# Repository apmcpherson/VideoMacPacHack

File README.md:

# VideoMacPacHack

The VideoMacPacHack is a clone of the Video Mac Pac, a PDS video card for the Macintosh Portable designed in 1991 by Computer Care Inc. The Video Mac Pac provides monochrome (1-bit) video on an external display, with several resolutions selectable by a control panel.

The VideoMacPacHack aims to replicate the Video Mac Pac using original parts where possible, with modern substitutions in  cases where original parts are hard to source (e.g. GAL, miniature relay), or where the original design was unknown (the video adapter board).

## Contents

* `hardware/VideoMacPac`: PCB design for the VideoMacPacHack, 4 layers, made in Kicad
* `hardware/VGA_adapter`: PCB design for the VGA breakout board, 2 layers, made in EAGLE
* `software`: Video Mac Pac Control Panel, needed to load the card firmware and select resolution
* `photos`: Photos of the original and clone card
* `documentation`: Technical information on the hardware and software

## System Requirements and Operation

The VideoMacPacHack fits the PDS slot of the Macintosh Portable. It has been successfully tested in both M5120 (non-backlit) and M5126 (backlit) Portables. Based on the address space used by the card, it will probably only work on Portables with less than 8MB of RAM installed.

The VideoMacPacHack (like the original Video Mac Pac) requires its associated control panel to run (see `software`). The external screen will become active when the control panel loads, provided the external video adapter is attached at boot. If the Portable is put to sleep, the external display will not work until reboot.

## Acknowledgments

The Video Mac Pac was created by Computer Care Inc. in 1991, apparently based on the Lapis DisplayServer.

The VideoMacPacHack was designed by [Andrew McPherson](https://github.com/apmcpherson) with encouragement from [Tom Stepleton](https://github.com/stepleton) based on hardware in his collection. In the interest of historical preservation it is released into the public domain, with no warranty of any sort.

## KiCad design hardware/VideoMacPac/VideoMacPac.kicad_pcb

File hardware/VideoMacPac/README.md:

# VideoMacPacHack

These design materials are in the public domain, with no warranty whatsoever. See `documentation` on this repository for further design notes.

## Kicad files

* `VideoMacPac.pro`: Kicad project
* `VideoMacPac.sch`: Kicad schematic
* `VideoMacPac.kicad_pcb`: Kicad PCB design
* `VideoMacPac_schematic.pdf`: Schematic in PDF format

## Gerbers

This a 4-layer PCB which can be fabricated from the files in the `gerbers` directory.

* `VideoMacPac-F.Cu.gbr`: top copper
* `VideoMacPac-In1.Cu.gbr`: inner layer 1 copper
* `VideoMacPac-In2.Cu.gbr`: inner layer 2 copper
* `VideoMacPac-B.Cu.gbr`: bottom copper
* `VideoMacPac-F.SilkS.gbr`: top silkscreen
* `VideoMacPac-F.Mask.gbr`: top soldermask
* `VideoMacPac-B.Mask.gbr`: bottom soldermask
* `VideoMacPac-Edge.Cuts.gbr`: board outline
* `VideoMacPac.drl`: Excellon drill file

## Bill of Materials

| Name    | Value                                |
| ------- | ------------------------------------ |
| C1-C8   | 0.1uF axial capacitors               |
| J1      | 20-pin IDC header                    |
| J2      | 96-pin right-angle EuroDIN           |
| R1-R4   | 4.7k resistors                       |
| RN1-RN2 | 3x47 ohm SIP resistor networks       |
| RN3-RN4 | 4x47 ohm SIP resistor networks       |
| U1      | XC2018-100-PC84 (faster can be used) |
| U2      | 74F521 (DIP)                         |
| U3      | 74AHCT1G00 (SOT23)                   |
| U4      | 74F244 (DIP) -- do not substitute    |
| U5-U8   | MT42C4064Z-12 (faster can be used)   |
| U9      | TPS2030 (DIP)                        |
| X1      | 36MHz 4-pin oscillator               |
| X2      | 50.35MHz 4-pin oscillator            |
| X3      | 57.2832MHz 4-pin oscillator          |

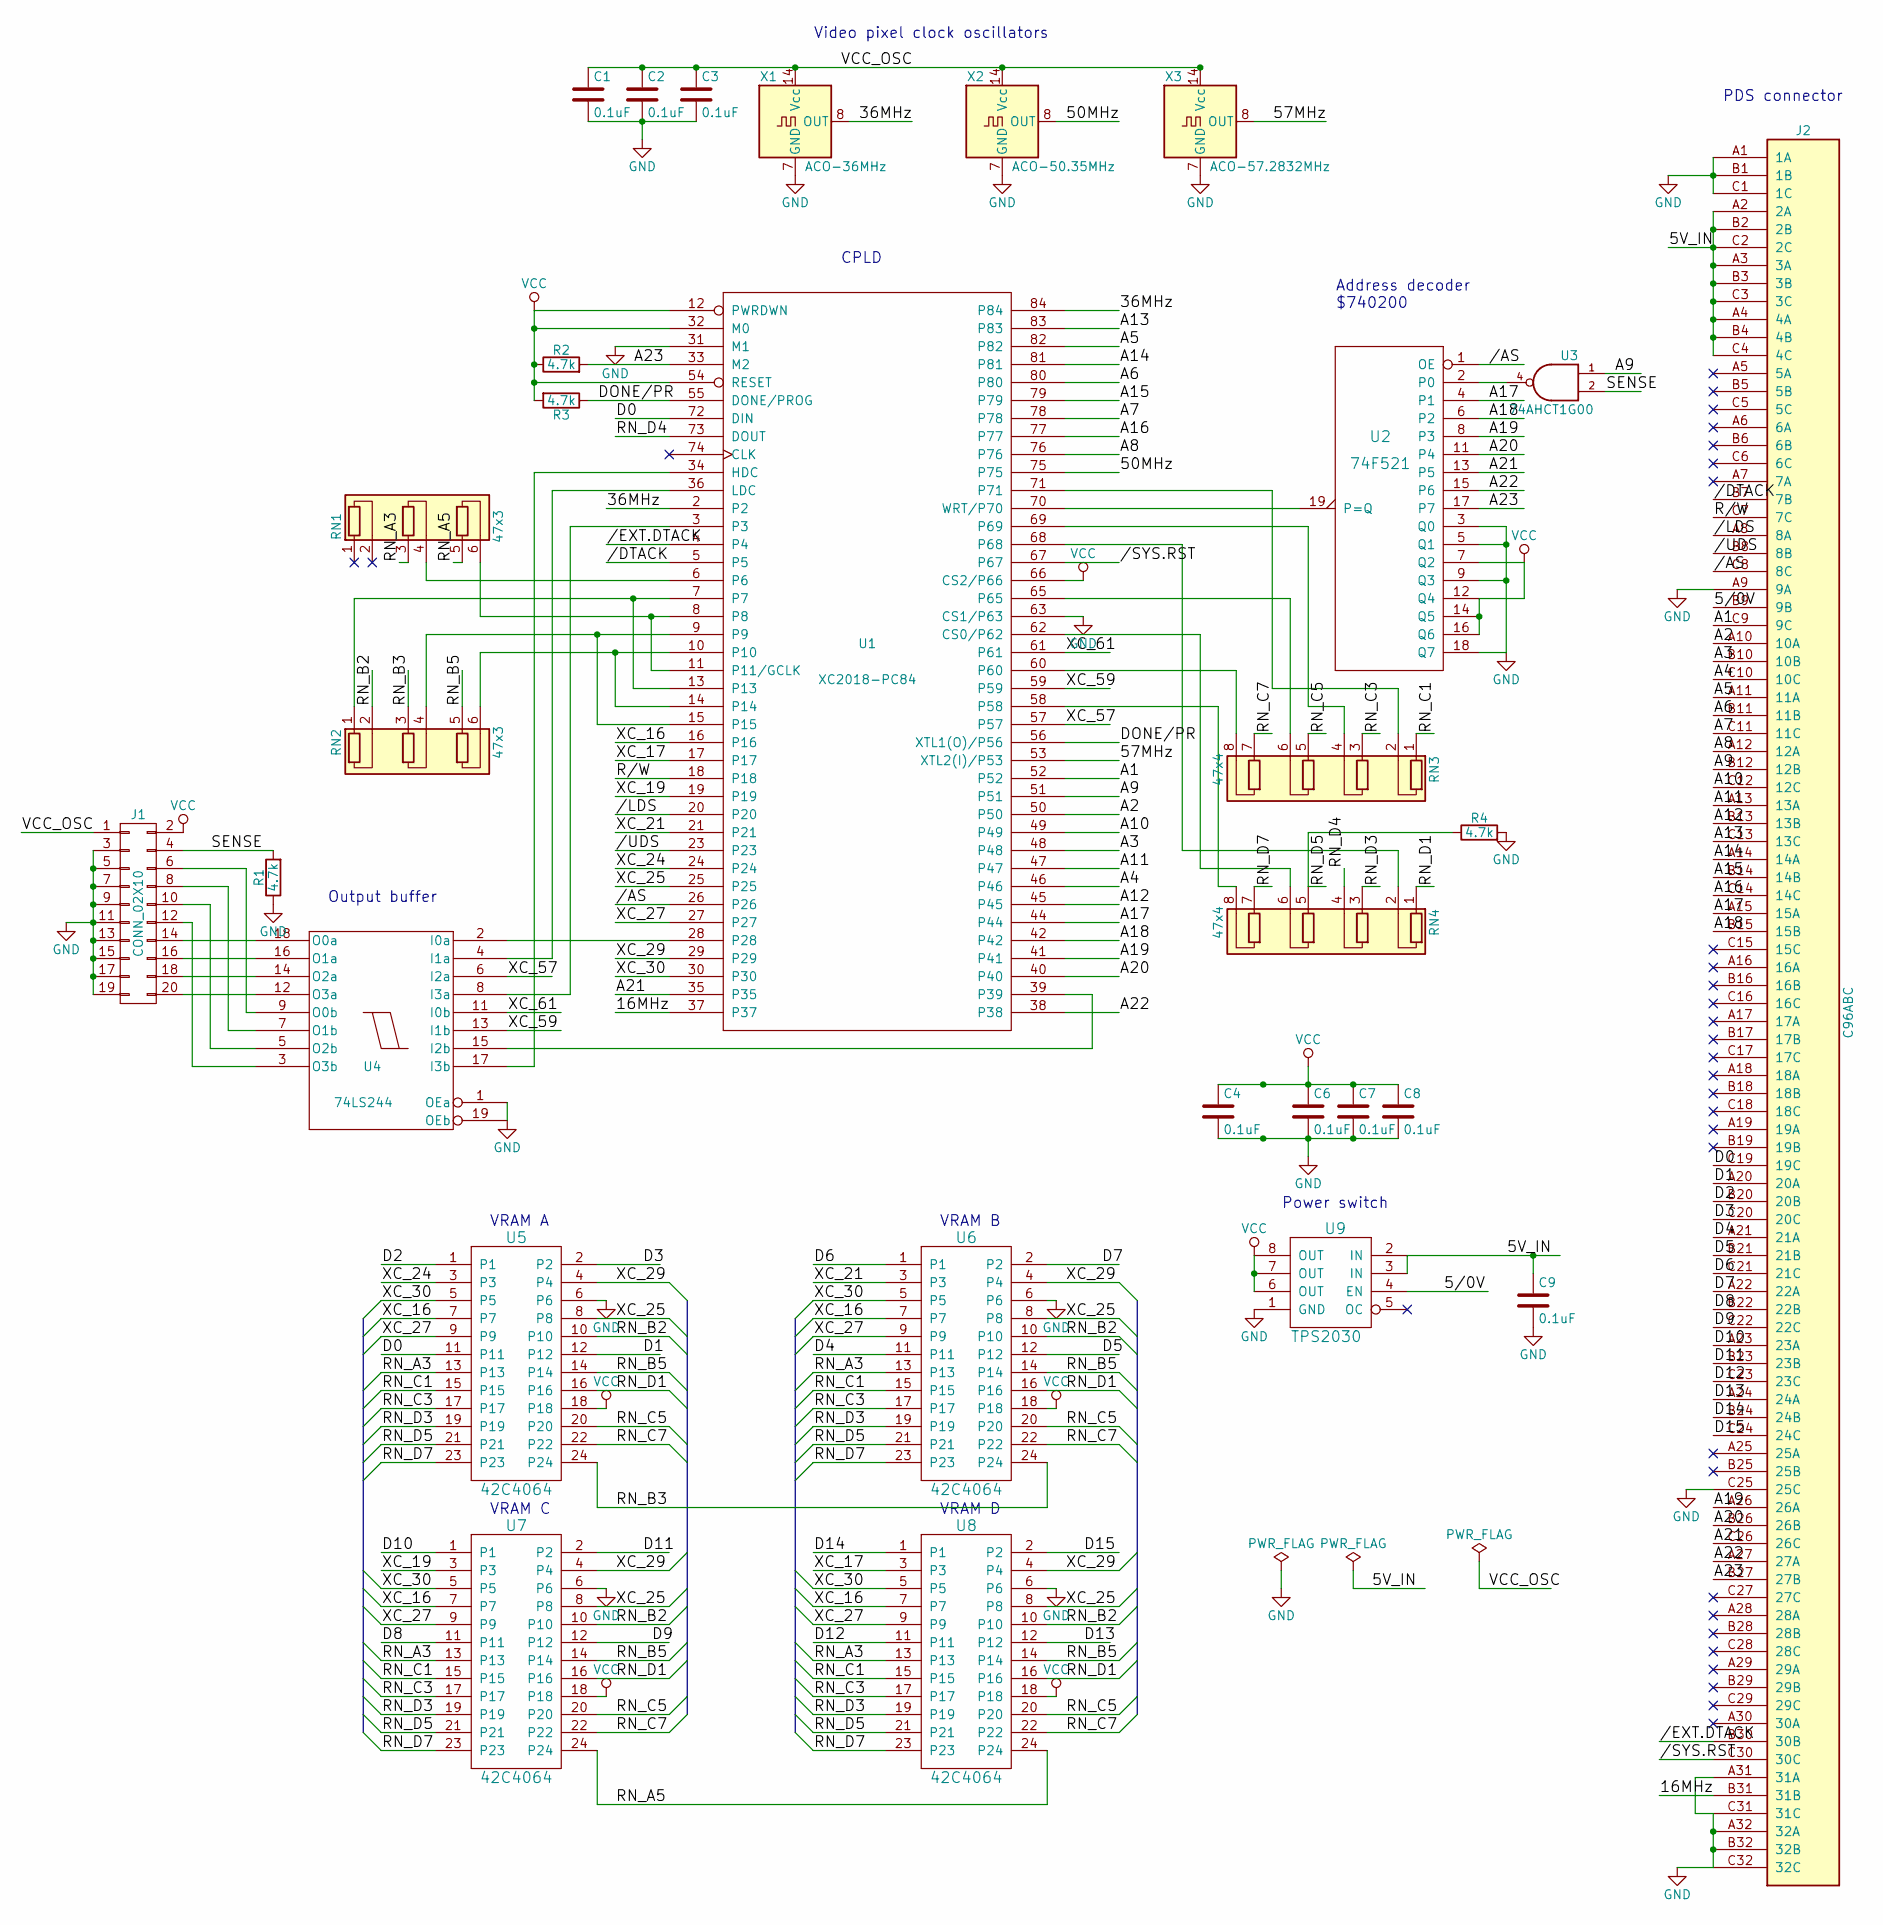
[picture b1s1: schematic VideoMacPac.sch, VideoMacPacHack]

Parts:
C1, C2, C3, C4, C6, C7, C8, C9: 0.1uF; C_Axial_L5.1mm_D3.1mm_P7.50mm_Horizontal
J1: CONN_02X10; IDC_Header_Straight_20pins
J2: C96ABC; C96ABCMD
R1, R2, R3, R4: 4.7k; R_Axial_DIN0207_L6.3mm_D2.5mm_P10.16mm_Horizontal
RN1, RN2: 47x3; R_Array_SIP6
RN3, RN4: 47x4; R_Array_SIP8
U1: XC2018-PC84; PLCC84
U2: 74F521; DIP-20_W7.62mm
U3: 74AHCT1G00; SOT-23-5
U4: 74LS244; DIP-20_W7.62mm
U5, U6, U7, U8: 42C4064; SIP24
U9: TPS2030; DIP-8_W7.62mm
X1: ACO-36MHz; Oscillator_DIP-14
X2: ACO-50.35MHz; Oscillator_DIP-14
X3: ACO-57.2832MHz; Oscillator_DIP-14

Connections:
/5/0V: J2.B9 (9B), U9.4 (EN)
/5V_IN: C9.1, J2.A2 (2A), J2.A3 (3A), J2.A4 (4A), J2.B2 (2B), J2.B3 (3B), J2.B4 (4B), J2.C2 (2C), J2.C3 (3C), J2.C4 (4C), U9.2 (IN), U9.3 (IN)
/16MHz: J2.B31 (31B), U1.37
/36MHz: U1.2, U1.84, X1.8 (OUT)
/50MHz: U1.75, X2.8 (OUT)
/57MHz: U1.53 (XTL2(I)/P53), X3.8 (OUT)
//AS: J2.C8 (8C), U1.26, U2.1 (OE)
//DTACK: J2.B7 (7B), U1.5
//EXT.DTACK: J2.B30 (30B), U1.4
//LDS: J2.A8 (8A), U1.20
//SYS.RST: J2.C30 (30C), U1.67
//UDS: J2.B8 (8B), U1.23
/A1: J2.C9 (9C), U1.52
/A2: J2.A10 (10A), U1.50
/A3: J2.B10 (10B), U1.48
/A4: J2.C10 (10C), U1.46
/A5: J2.A11 (11A), U1.82
/A6: J2.B11 (11B), U1.80
/A7: J2.C11 (11C), U1.78
/A8: J2.A12 (12A), U1.76
/A9: J2.B12 (12B), U1.51, U3.1
/A10: J2.C12 (12C), U1.49
/A11: J2.A13 (13A), U1.47
/A12: J2.B13 (13B), U1.45
/A13: J2.C13 (13C), U1.83
/A14: J2.A14 (14A), U1.81
/A15: J2.B14 (14B), U1.79
/A16: J2.C14 (14C), U1.77
/A17: J2.A15 (15A), U1.44, U2.4 (P1)
/A18: J2.B15 (15B), U1.42, U2.6 (P2)
/A19: J2.A26 (26A), U1.41, U2.8 (P3)
/A20: J2.B26 (26B), U1.40, U2.11 (P4)
/A21: J2.C26 (26C), U1.35, U2.13 (P5)
/A22: J2.A27 (27A), U1.38, U2.15 (P6)
/A23: J2.B27 (27B), R2.2, U1.33 (M2), U2.17 (P7)
/D0: J2.C19 (19C), U1.72 (DIN), U5.11
/D1: J2.A20 (20A), U5.12
/D2: J2.B20 (20B), U5.1
/D3: J2.C20 (20C), U5.2
/D4: J2.A21 (21A), U6.11
/D5: J2.B21 (21B), U6.12
/D6: J2.C21 (21C), U6.1
/D7: J2.A22 (22A), U6.2
/D8: J2.B22 (22B), U7.11
/D9: J2.C22 (22C), U7.12
/D10: J2.A23 (23A), U7.1
/D11: J2.B23 (23B), U7.2
/D12: J2.C23 (23C), U8.11
/D13: J2.A24 (24A), U8.12
/D14: J2.B24 (24B), U8.1
/D15: J2.C24 (24C), U8.2
/DONE/PR: R3.1, U1.55 (DONE/PROG), U1.56 (XTL1(O)/P56)
/R/W: J2.C7 (7C), U1.18
/RN_A3: RN1.3 (R2.1), U5.13, U6.13, U7.13, U8.13
/RN_A5: RN1.5 (R3.1), U7.24, U8.24
/RN_B2: RN2.2 (R1.2), U5.10, U6.10, U7.10, U8.10
/RN_B3: RN2.3 (R2.1), U5.24, U6.24
/RN_B5: RN2.5 (R3.1), U5.14, U6.14, U7.14, U8.14
/RN_C1: RN3.1 (R1.1), U5.15, U6.15, U7.15, U8.15
/RN_C3: RN3.3 (R2.1), U5.17, U6.17, U7.17, U8.17
/RN_C5: RN3.5 (R3.1), U5.20, U6.20, U7.20, U8.20
/RN_C7: RN3.7 (R4.1), U5.22, U6.22, U7.22, U8.22
/RN_D1: RN4.1 (R1.1), U5.16, U6.16, U7.16, U8.16
/RN_D3: RN4.3 (R2.1), U5.19, U6.19, U7.19, U8.19
/RN_D4: RN4.4 (R2.2), U1.73 (DOUT)
/RN_D5: R4.1, RN4.5 (R3.1), U5.21, U6.21, U7.21, U8.21
/RN_D7: RN4.7 (R4.1), U5.23, U6.23, U7.23, U8.23
/SENSE: J1.4, R1.2, U3.2
/VCC_OSC: C1.1, C2.1, C3.1, J1.1, X1.14 (Vcc), X2.14 (Vcc), X3.14 (Vcc)
/XC_16: U1.16, U5.7, U6.7, U7.7, U8.7
/XC_17: U1.17, U8.3
/XC_19: U1.19, U7.3
/XC_21: U1.21, U6.3
/XC_24: U1.24, U5.3
/XC_25: U1.25, U5.8, U6.8, U7.8, U8.8
/XC_27: U1.27, U5.9, U6.9, U7.9, U8.9
/XC_29: U1.29, U5.4, U6.4, U7.4, U8.4
/XC_30: U1.30, U5.5, U6.5, U7.5, U8.5
/XC_57: U1.57, U4.6 (I2a)
/XC_59: U1.59, U4.13 (I1b)
/XC_61: U1.61, U4.11 (I0b)
GND: C1.2, C2.2, C3.2, C4.2, C6.2, C7.2, C8.2, C9.2, J1.3, J1.5, J1.7, J1.9, J1.11, J1.13, J1.15, J1.17, J1.19, J2.A1 (1A), J2.A9 (9A), J2.A31 (31A), J2.A32 (32A), J2.B1 (1B), J2.B32 (32B), J2.C1 (1C), J2.C25 (25C), J2.C31 (31C), J2.C32 (32C), R1.1, R4.2, U1.1 (GND), U1.31 (M1), U1.43 (GND), U1.63 (CS1/P63), U2.3 (Q0), U2.5 (Q1), U2.9 (Q3), U2.10 (GND), U2.18 (Q7), U3.3 (GND), U4.1 (OEa), U4.10 (GND), U4.19 (OEb), U5.6, U6.6, U7.6, U8.6, U9.1 (GND), X1.7 (GND), X2.7 (GND), X3.7 (GND)
unnamed: J1.6, U4.9 (O0b)
unnamed: J1.8, U4.7 (O1b)
unnamed: J1.10, U4.5 (O2b)
unnamed: J1.12, U4.3 (O3b)
unnamed: J1.14, U4.18 (O0a)
unnamed: J1.16, U4.16 (O1a)
unnamed: J1.18, U4.14 (O2a)
unnamed: J1.20, U4.12 (O3a)
unnamed: RN1.4 (R2.2), U1.6
unnamed: RN1.6 (R3.2), U1.8, U1.11 (P11/GCLK)
unnamed: RN2.1 (R1.1), U1.7, U1.13
unnamed: RN2.4 (R2.2), U1.9, U1.15
unnamed: RN2.6 (R3.2), U1.10, U1.14
unnamed: RN3.2 (R1.2), U1.71
unnamed: RN3.4 (R2.2), U1.69
unnamed: RN3.6 (R3.2), U1.65
unnamed: RN3.8 (R4.2), U1.60
unnamed: RN4.2 (R1.2), U1.68
unnamed: RN4.6 (R3.2), U1.62 (CS0/P62)
unnamed: RN4.8 (R4.2), U1.58
unnamed: U1.3, U4.8 (I3a)
unnamed: U1.28, U4.2 (I0a)
unnamed: U1.34 (HDC), U4.17 (I3b)
unnamed: U1.36 (LDC), U4.4 (I1a)
unnamed: U1.39, U4.15 (I2b)
unnamed: U1.70 (WRT/P70), U2.19 (P=Q)
unnamed: U2.2 (P0), U3.4
VCC: C4.1, C6.1, C7.1, C8.1, J1.2, R2.1, R3.2, U1.12 (PWRDWN), U1.22 (VCC), U1.32 (M0), U1.54 (RESET), U1.64 (VCC), U1.66 (CS2/P66), U2.7 (Q2), U2.12 (Q4), U2.14 (Q5), U2.16 (Q6), U2.20 (VCC), U3.5 (VCC), U4.20 (VCC), U5.18, U6.18, U7.18, U8.18, U9.6 (OUT), U9.7 (OUT), U9.8 (OUT)

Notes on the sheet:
VRAM A
VRAM B
VRAM C
VRAM D
Power switch
Address decoder $740200
Output buffer
CPLD
Video pixel clock oscillators
PDS connector

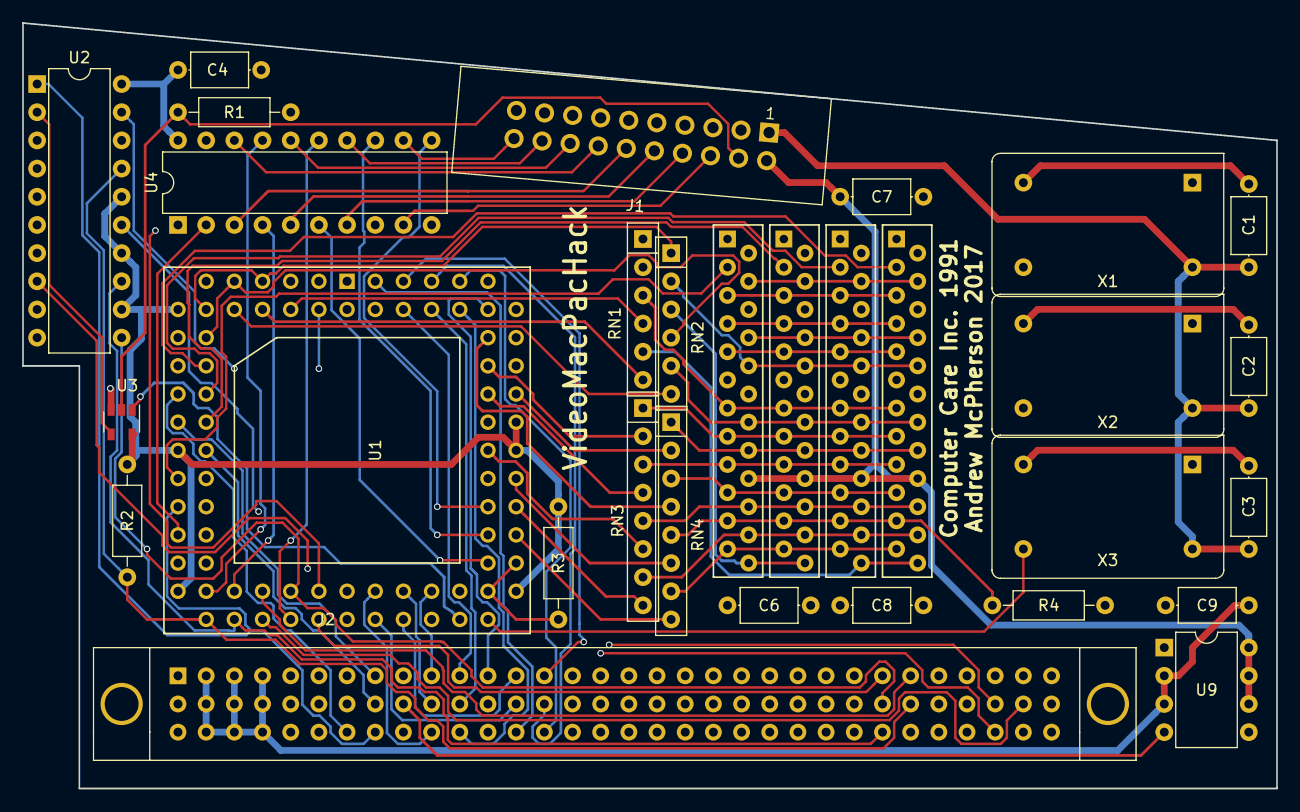
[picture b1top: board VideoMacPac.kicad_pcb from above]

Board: 4 copper layers, 113.0 x 69.0 mm, 30 parts (0 on the bottom side), 110 nets.

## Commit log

2020-04-06 Added documentation on VMP hardware and software
2020-04-06 Added documentation on the VMPH and adapter
2020-04-06 Added README to VMPH design
2020-04-06 Added README for VGA adapter
2020-04-06 Added README to documentation
2020-04-06 Added photo to main README
2020-04-06 URL fix for README photo
